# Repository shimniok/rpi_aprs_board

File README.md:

# Raspberry Pi APRS Interface Board

This board is designed to inteface a 2M ham radio with a Raspberry Pi running APRS software such as 
[direwolf](https://github.com/wb2osz/direwolf). Features DCD (Data Carrier Detect) and PTT (Push-To-Talk) GPIO and indicator 
LEDs.

I built this board for use with a Radio Shack HTX-212 I picked up cheap at a hamfest.

# HTX-212 Pinout

On the "XCVR" side of the board, solder jumper wires into wire pads labeled SPK/GND, and solder the other ends to a 3.5mm 
audio jack. Use a 3.5mm audio cable (mono is fine) to connext the radio's external speaker to this SPK jack. Use an RJ45 mic 
cable in the Mic jack of the radio and connect the 5V, PTT, MIC, and GND wire pads to the appropriate wires per the pinout 
image above and as below.

 * Pin 2 - GND
 * Pin 5 - MIC
 * Pin 6 - PTT
 * Pin 7 - 5V

# Raspberry Pi Hookup

You'll need an audio board with mic and speaker/headphone jack(s). You can either use a USB audio board or one that plugs 
into the RPi GPIO pins like these:

 * [Adafruit I2S Audio Bonnet](https://www.adafruit.com/product/4037?gclid=CjwKCAjwwZrmBRA7EiwA4iMzBJIsz_BS15PQMNVDndOI5iDkNbGunKcJ2TeuTTbweKNQdpY2VGxX5RoCWLQQAvD_BwE)
 * [Fe-Pi Audio Z (V2)](https://pinout.xyz/pinout/fe_pi_audio_z_v2)

Using jumper wire soldered into wire pads on the "RPi" side of the board, connect the MIC/GND to an 3.5mm audio jack, connect 
SPK/GND to another 3.5mm audio jack. Use two 3.5mm audio cables to connect to your audio board as follows. MIC goes to RPi 
mic jack. SPK goes to RPi external speaker jack. Then, solder jumper wire to the DCD and PTT wire pads, and connect to 
active high pins on the Raspberry Pi. I use GPIO17 and GPIO27. Ground is provided through the audio cables

# Adjusting Audio Levels

Adjust the MIC and SPK potentiometers in the middle. Now boot your Raspberry Pi and turn on your radio with an antenna 
attached and tune to 144.390MHz (APRS frequency). Launch direwolf after installing and setting up your direwolf.conf per the 
Direwolf User Guide. For now, disable beaconing.

## Adjust radio output level

Adjust radio volume and the SPK potentiometer until direwolf reports audio level of about 50 for most stations.  

## Adjust radio input level

You'll need an oscilloscope for this. Tune the radio to an unused packet band. Stop direwolf and reconfigure it to transmit 
every 5 seconds, and restart. Use the oscilloscope probe to display the waveform at the XCVR MIC output wirepad. Adjust the 
MIC potentiometer as high as it will go without clipping the peak of the signal.

You may need to adjust the Raspberry Pi's output level. Keep in mind that USB audio boards may "forget" alsamixer levels you
set should the board become unplugged.

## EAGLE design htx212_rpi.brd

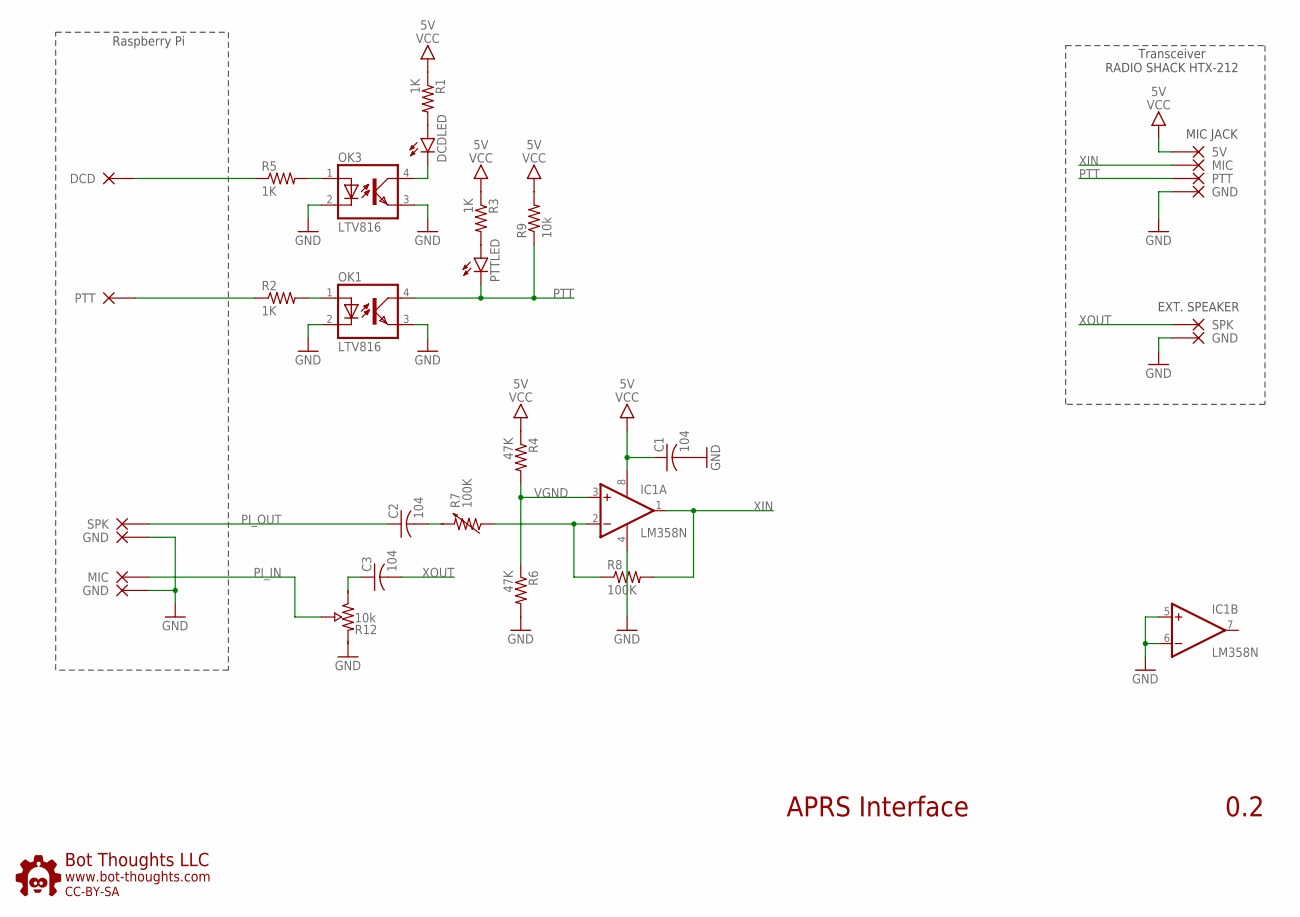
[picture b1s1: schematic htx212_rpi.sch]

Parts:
C1, C2: 104; C075
C3: 104; C050
DCDLED: LED5MMRA
IC1: LM358N; DIL08
OK1, OK3: LTV816; DIL04
PTTLED: LED5MMRA
R1, R2, R3, R5: 1K; 0204/7
R4, R6: 47K; 0204/7
R7: 100K; CA6V
R8: 100K; 0204/7
R9: 10k; 0204/7
R12: 10k; CA6V
U$3: BTLOGO-LOGO-MD; BTLOGOM
X1, X7: MIC; PAD_22GA
X2, X5, X8, X13: GND; PAD_22GA
X3: PTT; PAD_22GA
X4: 5V; PAD_22GA
X6, X12: SPK; PAD_22GA
X9: PTT; PAD_24GA
X15: DCD; PAD_24GA

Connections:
DCD_CTL: R5.1, X15.P$1
GND: C1.2 (-), IC1.4 (V-), IC1.5 (+IN), IC1.6 (-IN), OK1.2 (C), OK1.3 (EMIT), OK3.2 (C), OK3.3 (EMIT), R6.2, R12.E (B), X2.P$1, X5.P$1, X8.P$1, X13.P$1
unnamed: OK1.1 (A), R2.2
unnamed: DCDLED.A, R1.2
unnamed: DCDLED.C, OK3.4 (COL)
unnamed: PTTLED.A, R3.2
unnamed: OK3.1 (A), R5.2
unnamed: C3.1 (+), R12.A
unnamed: IC1.2 (-IN), R7.S (WIPER), R8.1
unnamed: C2.2 (-), R7.E (B)
PI_IN: R12.S (WIPER), X7.P$1
PI_OUT: C2.1 (+), X6.P$1
PTT: OK1.4 (COL), PTTLED.C, R9.1, X3.P$1
PTT_CTL: R2.1, X9.P$1
VCC: C1.1 (+), IC1.8 (V+), R1.1, R3.1, R4.1, R9.2, X4.P$1
VGND: IC1.3 (+IN), R4.2, R6.1
XIN: IC1.1 (OUT), R8.2, X1.P$1
XOUT: C3.2 (-), X12.P$1

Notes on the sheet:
Raspberry Pi
Transceiver RADIO SHACK HTX-212
MIC JACK
EXT. SPEAKER
APRS Interface
0.2

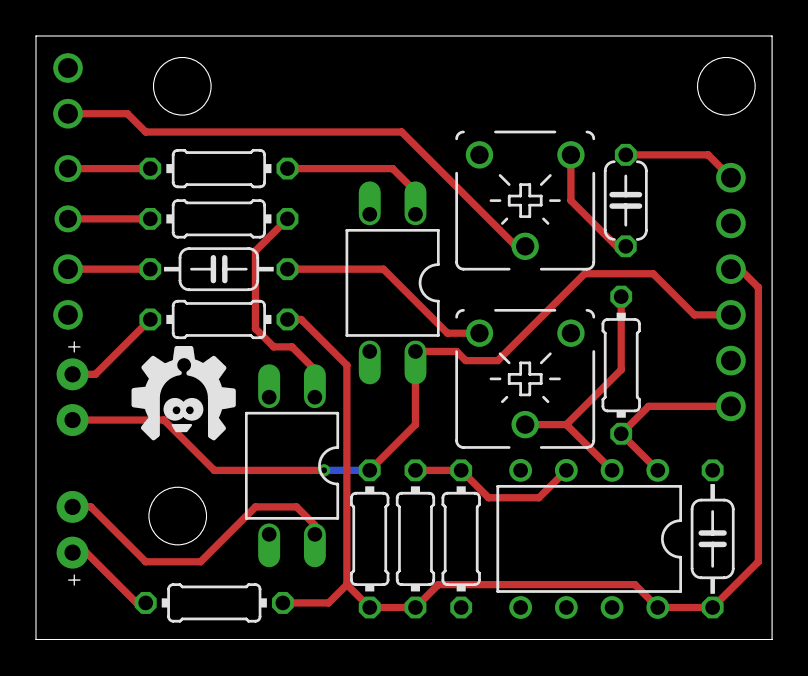
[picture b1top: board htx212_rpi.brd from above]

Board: 2 copper layers, 40.9 x 33.5 mm, 31 parts (0 on the bottom side), 18 nets.

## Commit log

2019-04-14 initial
2019-04-14 added zip
2019-04-29 PTT pull-down to pull-up on PTT, radio side.
2019-04-29 add gitignore for eagle stuff
2019-04-29 added images
2019-04-29 added photos
2019-04-29 Added hookup instructions
2019-04-29 Updated pinout
2019-04-29 Added audio level adjustment instructions

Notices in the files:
htx212_rpi.brd:
cc-by-sa
